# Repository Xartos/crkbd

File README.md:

# Fork purpose

The purpose of this fork is to replace the audio jack `ST-0277D00-052-142` for the v4 model and replace it with the `PJ-606-6A`

# Corne keyboard

The Corne keyboard is a split keyboard with 3x6 column staggered keys
and 3 thumb keys, based on [Helix](https://github.com/MakotoKurauchi/helix).
Crkbd stands for Corne Keyboard.

## Latest versions
- corne-cherry: for Cherry MX compatible switches

  - v4 Hotswappable ([JP](docs/corne-cherry/v4/buildguide_jp.md)/[EN](docs/corne-cherry/v4/buildguide_en.md))
  - v4 Soldering (will be released)
- corne-chocolate: for Kailh choc v1 and v2 switches
  - v4 Hotswappable ([JP](docs/corne-chocolate/v4/buildguide_jp.md)/[EN](docs/corne-chocolate/v4/buildguide_en.md)):
  - v4 Soldering (will be released)

## Old versions

- corne-classic: for Cherry MX compatible switches 
  - v1 Soldering: ([JP](docs/corne-classic/buildguide_jp.md)/[EN](docs/corne-classic/buildguide_en.md))
- corne-cherry: for Cherry MX compatible switches
  - v2 Hotswappable: ([JP](docs/corne-cherry/v2/buildguide_jp.md)/[EN](docs/corne-cherry/v2/buildguide_en.md))
  - v2 Hotswappable tilting version: ([tilting, JP](docs/corne-cherry/v2/buildguide_tilting_tenting_plate_jp.md)/[tilting, EN](docs/corne-cherry/v2/buildguide_tilting_tenting_plate_en.md)):
  - v3 Hotswappable: ([JP](docs/corne-cherry/v3/buildguide_jp.md)/[EN](docs/corne-cherry/v3/buildguide_en.md))
- corne-chocolate: for Kailh choc v1 switches
  - v2 Hotswappable: ([JP](docs/corne-chocolate/v2/buildguide_jp.md)/[EN](docs/corne-chocolate/v2/buildguide_en.md)):
- corne-light: for easy build with a simple PCB
  - v1 Soldering: ([JP](docs/corne-light/v1/buildguide_jp.md)/[EN](docs/corne-light/v1/buildguide_en.md)):
  - v2 Soldering: ([JP](docs/corne-light/v2/buildguide_low_edition_jp.md)/[EN](docs/corne-light/v2/buildguide_low_edition_en.md)):

## Images

### Cherry

### Chocolate

### Drawing

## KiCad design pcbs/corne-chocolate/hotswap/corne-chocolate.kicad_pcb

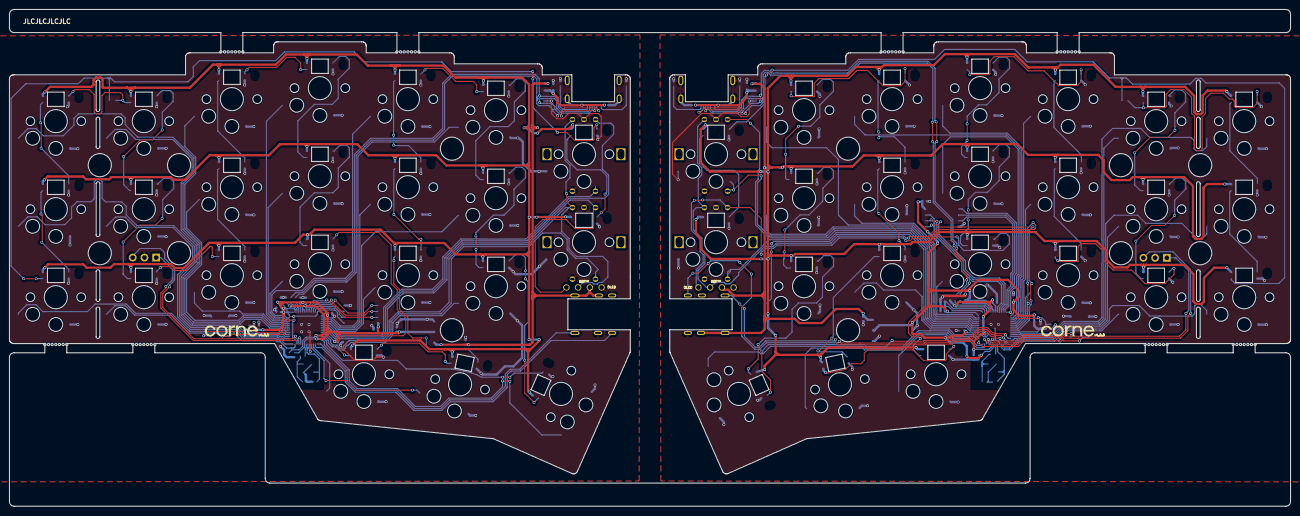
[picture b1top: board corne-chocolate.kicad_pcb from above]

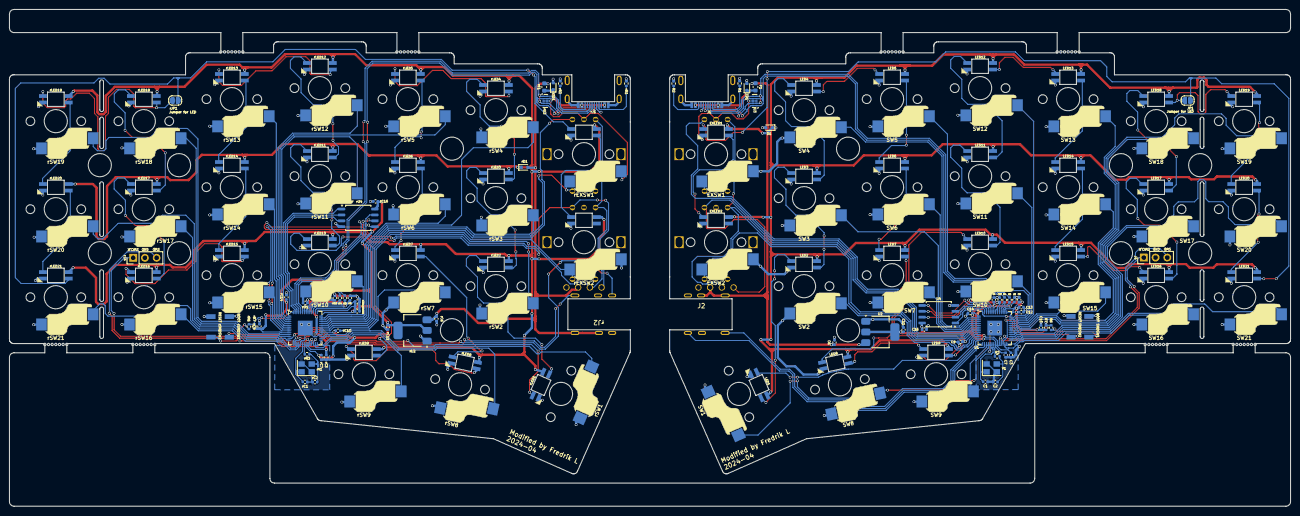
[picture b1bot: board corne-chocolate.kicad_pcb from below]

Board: 2 copper layers, 277.2 x 107.5 mm, 176 parts (166 on the bottom side), 152 nets.

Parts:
BT1, BT2, BT3, BT4: Breakaway Tabs; Breakaway_Tabs
C1, C2: 27p; C_0402_1005Metric
C3, C4, C7, C9, C10, C12, C13, C14, C15: 100n; C_0402_1005Metric
C5, C8, C16: 1u; C_0402_1005Metric
C6, C11: 10u; C_0402_1005Metric
D1: 1N4148WT; D_SOD-523
EXLED1, EXLED2: YS-SK6812MINI-E
EXSW1, EXSW2: RotaryEncoder_Switch; keyswitch_choc12_hotswap_1u_rotary_encoder_ec12
F1: BSMD0603-050-12V; Fuse_0603_1608Metric
J1: TYPE-C-31-M-13C
J2: PJ-606-6A
J3: Conn_01x04; OLED
J4: Conn_01x03; PinHeader_1x03_P2.54mm_Vertical
JP1: SolderJumper_2_Bridged; SolderJumper-2_P1.3mm_Open_RoundedPad1.0x1.5mm
LED1, LED2, LED3, LED4, LED5, LED6, LED7, LED8, LED9, LED10, LED11, LED12, LED13, LED14, LED15, LED16, LED17, LED18, LED19, LED20, LED21: YS-SK6812MINI-E
R1, R2: 5.1k; R_0402_1005Metric
R3, R6: 1k; R_0402_1005Metric
R4, R5: 27; R_0402_1005Metric
R7: 10k; R_0402_1005Metric
SMDSW1, SMDSW2: TS-1088R-02026
SW1: SW_Push; keyswitch_choc12_hotswap_1.5u
SW2, SW3, SW4, SW5, SW6, SW7, SW8, SW9, SW10, SW11, SW12, SW13, SW14, SW15, SW16, SW17, SW18, SW19, SW20, SW21: SW_Push; keyswitch_choc12_hotswap_1u
U1: RP2040; QFN-56-1EP_7x7mm_P0.4mm_EP3.2x3.2mm
U2: NCP1117LPST33T3G; SOT-223-3_TabPin2
U3: TPD4E05U06DQAR; USON-10_2.5x1.0mm_P0.5mm
U4: W25Q128JVSIQ; SOIC-8_5.23x5.23mm_P1.27mm
Y1: 12MHz 18pF; Crystal_SMD_3225-4Pin_3.2x2.5mm
ZD1: ESD5Z5V0C; D_SOD-523
rBT1, rBT2, rBT3, rBT4: Breakaway Tabs; Breakaway_Tabs
rC1, rC2: 27p; C_0402_1005Metric
rC3, rC4, rC7, rC9, rC10, rC12, rC13, rC14, rC15: 100n; C_0402_1005Metric
rC5, rC8, rC16: 1u; C_0402_1005Metric
rC6, rC11: 10u; C_0402_1005Metric
rD1: 1N4148WT; D_SOD-523
rEXLED1, rEXLED2: YS-SK6812MINI-E
rEXSW1, rEXSW2: RotaryEncoder_Switch; keyswitch_choc12_hotswap_1u_rotary_encoder_ec12
rF1: BSMD0603-050-12V; Fuse_0603_1608Metric
rJ1: TYPE-C-31-M-13C
rJ2: PJ-606-6A
rJ3: Conn_01x04; OLED
rJ4: Conn_01x03; PinHeader_1x03_P2.54mm_Vertical
rJP1: SolderJumper_2_Bridged; SolderJumper-2_P1.3mm_Open_RoundedPad1.0x1.5mm
rLED1, rLED2, rLED3, rLED4, rLED5, rLED6, rLED7, rLED8, rLED9, rLED10, rLED11, rLED12, rLED13, rLED14, rLED15, rLED16, rLED17, rLED18, rLED19, rLED20, rLED21: YS-SK6812MINI-E
rR1, rR2: 5.1k; R_0402_1005Metric
rR3, rR6: 1k; R_0402_1005Metric
rR4, rR5: 27; R_0402_1005Metric
rR7: 10k; R_0402_1005Metric
rSMDSW1, rSMDSW2: TS-1088R-02026
rSW1: SW_Push; keyswitch_choc12_hotswap_1.5u
rSW2, rSW3, rSW4, rSW5, rSW6, rSW7, rSW8, rSW9, rSW10, rSW11, rSW12, rSW13, rSW14, rSW15, rSW16, rSW17, rSW18, rSW19, rSW20, rSW21: SW_Push; keyswitch_choc12_hotswap_1u
rU1: RP2040; QFN-56-1EP_7x7mm_P0.4mm_EP3.2x3.2mm
rU2: NCP1117LPST33T3G; SOT-223-3_TabPin2
rU3: TPD4E05U06DQAR; USON-10_2.5x1.0mm_P0.5mm
rU4: W25Q128JVSIQ; SOIC-8_5.23x5.23mm_P1.27mm
rY1: 12MHz 18pF; Crystal_SMD_3225-4Pin_3.2x2.5mm
rZD1: ESD5Z5V0C; D_SOD-523

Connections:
+1V1: C3.1, C4.1, C5.1, U1.23 (DVDD), U1.45 (VREG_VOUT), U1.50 (DVDD)
+1V1R: rC3.1, rC4.1, rC5.1, rU1.23 (DVDD), rU1.45 (VREG_VOUT), rU1.50 (DVDD)
+3V3: C7.1, C8.1, C9.1, C10.1, C11.1, C12.1, C13.1, C14.1, C15.1, C16.1, R7.2, U1.1 (IOVDD), U1.10 (IOVDD), U1.22 (IOVDD), U1.32 (GPIO21), U1.33 (IOVDD), U1.42 (IOVDD), U1.43 (ADC_AVDD), U1.44 (VREG_IN), U1.48 (USB_VDD), U1.49 (IOVDD), U2.2 (VO), U4.8 (VCC)
+3V3R: rC7.1, rC8.1, rC9.1, rC10.1, rC11.1, rC12.1, rC13.1, rC14.1, rC15.1, rC16.1, rR7.2, rU1.1 (IOVDD), rU1.10 (IOVDD), rU1.22 (IOVDD), rU1.33 (IOVDD), rU1.42 (IOVDD), rU1.43 (ADC_AVDD), rU1.44 (VREG_IN), rU1.48 (USB_VDD), rU1.49 (IOVDD), rU2.2 (VO), rU4.8 (VCC)
+5V: C6.1, D1.2 (A), F1.2, J2.T, J3.3, U2.3 (VI)
+5VR: rC6.1, rD1.2 (A), rF1.2, rJ2.T, rJ3.3, rU2.3 (VI)
/left/D+: J1.A6 (D+), J1.B6 (D+), R4.1, U3.1 (D1+), U3.4 (D2+), U3.7 (NC), U3.10 (NC)
/left/D-: J1.A7 (D-), J1.B7 (D-), R5.2, U3.2 (D1-), U3.5 (D2-), U3.6 (NC), U3.9 (NC)
/left/KEY1: SW1.1, U1.14 (GPIO11)
/left/KEY2: SW2.1, U1.12 (GPIO9)
/left/KEY3: SW3.1, U1.4 (GPIO2)
/left/KEY4: SW4.1, U1.2 (GPIO0)
/left/KEY5: SW5.1, U1.41 (GPIO29_ADC3)
/left/KEY6: SW6.1, U1.3 (GPIO1)
/left/KEY7: SW7.1, U1.5 (GPIO3)
/left/KEY8: SW8.1, U1.18 (GPIO15)
/left/KEY9: SW9.1, U1.17 (GPIO14)
/left/KEY10: SW10.1, U1.40 (GPIO28_ADC2)
/left/KEY11: SW11.1, U1.39 (GPIO27_ADC1)
/left/KEY12: SW12.1, U1.38 (GPIO26_ADC0)
/left/KEY13: SW13.1, U1.35 (GPIO23)
/left/KEY14: SW14.1, U1.36 (GPIO24)
/left/KEY15: SW15.1, U1.37 (GPIO25)
/left/KEY16: SW16.1, U1.27 (GPIO16)
/left/KEY17: SW17.1, U1.29 (GPIO18)
/left/KEY18: SW18.1, U1.31 (GPIO20)
/left/KEY19: SW19.1, U1.34 (GPIO22)
/left/KEY20: SW20.1, U1.30 (GPIO19)
/left/KEY21: SW21.1, U1.28 (GPIO17)
/left/KEYEX1: EXSW1.S2, U1.6 (GPIO4)
/left/KEYEX2: EXSW2.S2, U1.11 (GPIO8)
/left/LED: LED1.4 (DIN), U1.13 (GPIO10)
/left/QSPI_SCLK: U1.52 (QSPI_SCLK), U4.6 (CLK)
/left/QSPI_SD0: U1.53 (QSPI_SD0), U4.5 (DI(IO0))
/left/QSPI_SD1: U1.55 (QSPI_SD1), U4.2 (DO(IO1))
/left/QSPI_SD2: U1.54 (QSPI_SD2), U4.3 (IO2)
/left/QSPI_SD3: U1.51 (QSPI_SD3), U4.7 (IO3)
/left/QSPI_SS: R6.1, R7.1, U1.56 (QSPI_SS), U4.1 (~CS)
/left/RE0A: EXSW1.A, U1.7 (GPIO5)
/left/RE1A: EXSW2.A, J3.1, U1.8 (GPIO6)
/left/REB: EXSW1.B, EXSW2.B, J3.2, U1.9 (GPIO7)
/left/RX: J2.R1, U1.16 (GPIO13)
/left/SWCLK: J4.1, U1.24 (SWCLK)
/left/SWD: J4.3, U1.25 (SWD)
/left/TX: J2.R2, U1.15 (GPIO12)
/right/D+: rJ1.A6 (D+), rJ1.B6 (D+), rR4.1, rU3.1 (D1+), rU3.4 (D2+), rU3.7 (NC), rU3.10 (NC)
/right/D-: rJ1.A7 (D-), rJ1.B7 (D-), rR5.2, rU3.2 (D1-), rU3.5 (D2-), rU3.6 (NC), rU3.9 (NC)
/right/KEY1: rSW1.1, rU1.30 (GPIO19)
/right/KEY2: rSW2.1, rU1.34 (GPIO22)
/right/KEY3: rSW3.1, rU1.38 (GPIO26_ADC0)
/right/KEY4: rSW4.1, rU1.39 (GPIO27_ADC1)
/right/KEY5: rSW5.1, rU1.3 (GPIO1)
/right/KEY6: rSW6.1, rU1.40 (GPIO28_ADC2)
/right/KEY7: rSW7.1, rU1.31 (GPIO20)
/right/KEY8: rSW8.1, rU1.28 (GPIO17)
/right/KEY9: rSW9.1, rU1.27 (GPIO16)
/right/KEY10: rSW10.1, rU1.41 (GPIO29_ADC3)
/right/KEY11: rSW11.1, rU1.2 (GPIO0)
/right/KEY12: rSW12.1, rU1.4 (GPIO2)
/right/KEY13: rSW13.1, rU1.5 (GPIO3)
/right/KEY14: rSW14.1, rU1.6 (GPIO4)
/right/KEY15: rSW15.1, rU1.7 (GPIO5)
/right/KEY16: rSW16.1, rU1.29 (GPIO18)
/right/KEY17: rSW17.1, rU1.17 (GPIO14)
/right/KEY18: rSW18.1, rU1.12 (GPIO9)
/right/KEY19: rSW19.1, rU1.11 (GPIO8)
/right/KEY20: rSW20.1, rU1.14 (GPIO11)
/right/KEY21: rSW21.1, rU1.18 (GPIO15)
/right/KEYEX1: rEXSW1.S2, rU1.37 (GPIO25)
/right/KEYEX2: rEXSW2.S2, rU1.35 (GPIO23)
/right/LED: rLED1.4 (DIN), rU1.13 (GPIO10)
/right/QSPI_SCLK: rU1.52 (QSPI_SCLK), rU4.6 (CLK)
/right/QSPI_SD0: rU1.53 (QSPI_SD0), rU4.5 (DI(IO0))
/right/QSPI_SD1: rU1.55 (QSPI_SD1), rU4.2 (DO(IO1))
/right/QSPI_SD2: rU1.54 (QSPI_SD2), rU4.3 (IO2)
/right/QSPI_SD3: rU1.51 (QSPI_SD3), rU4.7 (IO3)
/right/QSPI_SS: rR6.1, rR7.1, rU1.56 (QSPI_SS), rU4.1 (~CS)
/right/RE0A: rEXSW1.A, rU1.36 (GPIO24)
/right/RE1A: rEXSW2.A, rJ3.1, rU1.8 (GPIO6)
/right/REB: rEXSW1.B, rEXSW2.B, rJ3.2, rU1.9 (GPIO7)
/right/RX: rJ2.R2, rU1.16 (GPIO13)
/right/SWCLK: rJ4.1, rU1.24 (SWCLK)
/right/SWD: rJ4.3, rU1.25 (SWD)
/right/TX: rJ2.R1, rU1.15 (GPIO12)
GND: C1.2, C2.2, C3.2, C4.2, C5.2, C6.2, C7.2, C8.2, C9.2, C10.2, C11.2, C12.2, C13.2, C14.2, C15.2, C16.2, EXLED1.3 (VSS), EXLED2.3 (VSS), EXSW1.C, EXSW1.S1, EXSW2.C, EXSW2.S1, J1.A1 (GND), J1.A12 (GND), J1.B1 (GND), J1.B12 (GND), J1.S1 (SHIELD), J2.S, J3.4, J4.2, LED1.3 (VSS), LED2.3 (VSS), LED3.3 (VSS), LED4.3 (VSS), LED5.3 (VSS), LED6.3 (VSS), LED7.3 (VSS), LED8.3 (VSS), LED9.3 (VSS), LED10.3 (VSS), LED11.3 (VSS), LED12.3 (VSS), LED13.3 (VSS), LED14.3 (VSS), LED15.3 (VSS), LED16.3 (VSS), LED17.3 (VSS), LED18.3 (VSS), LED19.3 (VSS), LED20.3 (VSS), LED21.3 (VSS), R1.1, R2.1, SMDSW1.1, SMDSW2.1, SW1.2, SW2.2, SW3.2, SW4.2, SW5.2, SW6.2, SW7.2, SW8.2, SW9.2, SW10.2, SW11.2, SW12.2, SW13.2, SW14.2, SW15.2, SW16.2, SW17.2, SW18.2, SW19.2, SW20.2, SW21.2, U1.19 (TESTEN), U1.57 (GND), U2.1 (GND), U3.3 (GND), U3.8 (GND), U4.4 (GND), Y1.2, Y1.4, ZD1.2 (A)
GNDR: rC1.2, rC2.2, rC3.2, rC4.2, rC5.2, rC6.2, rC7.2, rC8.2, rC9.2, rC10.2, rC11.2, rC12.2, rC13.2, rC14.2, rC15.2, rC16.2, rEXLED1.3 (VSS), rEXLED2.3 (VSS), rEXSW1.C, rEXSW1.S1, rEXSW2.C, rEXSW2.S1, rJ1.A1 (GND), rJ1.A12 (GND), rJ1.B1 (GND), rJ1.B12 (GND), rJ1.S1 (SHIELD), rJ2.S, rJ3.4, rJ4.2, rLED1.3 (VSS), rLED2.3 (VSS), rLED3.3 (VSS), rLED4.3 (VSS), rLED5.3 (VSS), rLED6.3 (VSS), rLED7.3 (VSS), rLED8.3 (VSS), rLED9.3 (VSS), rLED10.3 (VSS), rLED11.3 (VSS), rLED12.3 (VSS), rLED13.3 (VSS), rLED14.3 (VSS), rLED15.3 (VSS), rLED16.3 (VSS), rLED17.3 (VSS), rLED18.3 (VSS), rLED19.3 (VSS), rLED20.3 (VSS), rLED21.3 (VSS), rR1.1, rR2.1, rSMDSW1.1, rSMDSW2.1, rSW1.2, rSW2.2, rSW3.2, rSW4.2, rSW5.2, rSW6.2, rSW7.2, rSW8.2, rSW9.2, rSW10.2, rSW11.2, rSW12.2, rSW13.2, rSW14.2, rSW15.2, rSW16.2, rSW17.2, rSW18.2, rSW19.2, rSW20.2, rSW21.2, rU1.19 (TESTEN), rU1.32 (GPIO21), rU1.57 (GND), rU2.1 (GND), rU3.3 (GND), rU3.8 (GND), rU4.4 (GND), rY1.2, rY1.4, rZD1.2 (A)
unnamed: C2.1, R3.1, Y1.3
unnamed: D1.1 (K), EXLED1.1 (VDD), EXLED2.1 (VDD), LED1.1 (VDD), LED2.1 (VDD), LED3.1 (VDD), LED4.1 (VDD), LED5.1 (VDD), LED6.1 (VDD), LED7.1 (VDD), LED8.1 (VDD), LED9.1 (VDD), LED10.1 (VDD), LED11.1 (VDD), LED12.1 (VDD), LED13.1 (VDD), LED14.1 (VDD), LED15.1 (VDD), LED16.1 (VDD), LED17.1 (VDD), LED18.1 (VDD), LED19.1 (VDD), LED20.1 (VDD), LED21.1 (VDD)
unnamed: EXLED1.4 (DIN), JP1.2 (B), LED21.2 (DOUT)
unnamed: EXLED1.2 (DOUT), EXLED2.4 (DIN)
unnamed: J1.A5 (CC1), R1.2
unnamed: J1.B5 (CC2), R2.2
unnamed: JP1.1 (A), LED18.2 (DOUT), LED19.4 (DIN)
unnamed: LED1.2 (DOUT), LED2.4 (DIN)
unnamed: LED2.2 (DOUT), LED3.4 (DIN)
unnamed: LED3.2 (DOUT), LED4.4 (DIN)
unnamed: LED4.2 (DOUT), LED5.4 (DIN)
unnamed: LED5.2 (DOUT), LED6.4 (DIN)
unnamed: LED6.2 (DOUT), LED7.4 (DIN)
unnamed: LED7.2 (DOUT), LED8.4 (DIN)
unnamed: LED8.2 (DOUT), LED9.4 (DIN)
unnamed: LED9.2 (DOUT), LED10.4 (DIN)
unnamed: LED10.2 (DOUT), LED11.4 (DIN)
unnamed: LED11.2 (DOUT), LED12.4 (DIN)
unnamed: LED12.2 (DOUT), LED13.4 (DIN)
unnamed: LED13.2 (DOUT), LED14.4 (DIN)
unnamed: LED14.2 (DOUT), LED15.4 (DIN)
unnamed: LED15.2 (DOUT), LED16.4 (DIN)
unnamed: LED16.2 (DOUT), LED17.4 (DIN)
unnamed: LED17.2 (DOUT), LED18.4 (DIN)
unnamed: LED19.2 (DOUT), LED20.4 (DIN)
unnamed: LED20.2 (DOUT), LED21.4 (DIN)
unnamed: R6.2, SMDSW1.2
unnamed: SMDSW2.2, U1.26 (RUN)
unnamed: R5.1, U1.46 (USB_DM)
unnamed: R4.2, U1.47 (USB_DP)
unnamed: C1.1, U1.20 (XIN), Y1.1
unnamed: R3.2, U1.21 (XOUT)
unnamed: rC2.1, rR3.1, rY1.3
unnamed: rD1.1 (K), rEXLED1.1 (VDD), rEXLED2.1 (VDD), rLED1.1 (VDD), rLED2.1 (VDD), rLED3.1 (VDD), rLED4.1 (VDD), rLED5.1 (VDD), rLED6.1 (VDD), rLED7.1 (VDD), rLED8.1 (VDD), rLED9.1 (VDD), rLED10.1 (VDD), rLED11.1 (VDD), rLED12.1 (VDD), rLED13.1 (VDD), rLED14.1 (VDD), rLED15.1 (VDD), rLED16.1 (VDD), rLED17.1 (VDD), rLED18.1 (VDD), rLED19.1 (VDD), rLED20.1 (VDD), rLED21.1 (VDD)
unnamed: rEXLED1.4 (DIN), rJP1.2 (B), rLED21.2 (DOUT)
unnamed: rEXLED1.2 (DOUT), rEXLED2.4 (DIN)
unnamed: rJ1.A5 (CC1), rR1.2
unnamed: rJ1.B5 (CC2), rR2.2
unnamed: rJP1.1 (A), rLED18.2 (DOUT), rLED19.4 (DIN)
unnamed: rLED1.2 (DOUT), rLED2.4 (DIN)
unnamed: rLED2.2 (DOUT), rLED3.4 (DIN)
unnamed: rLED3.2 (DOUT), rLED4.4 (DIN)
unnamed: rLED4.2 (DOUT), rLED5.4 (DIN)
unnamed: rLED5.2 (DOUT), rLED6.4 (DIN)
unnamed: rLED6.2 (DOUT), rLED7.4 (DIN)
unnamed: rLED7.2 (DOUT), rLED8.4 (DIN)
unnamed: rLED8.2 (DOUT), rLED9.4 (DIN)
unnamed: rLED9.2 (DOUT), rLED10.4 (DIN)
unnamed: rLED10.2 (DOUT), rLED11.4 (DIN)
unnamed: rLED11.2 (DOUT), rLED12.4 (DIN)
unnamed: rLED12.2 (DOUT), rLED13.4 (DIN)
unnamed: rLED13.2 (DOUT), rLED14.4 (DIN)
unnamed: rLED14.2 (DOUT), rLED15.4 (DIN)
unnamed: rLED15.2 (DOUT), rLED16.4 (DIN)
unnamed: rLED16.2 (DOUT), rLED17.4 (DIN)
unnamed: rLED17.2 (DOUT), rLED18.4 (DIN)
unnamed: rLED19.2 (DOUT), rLED20.4 (DIN)
unnamed: rLED20.2 (DOUT), rLED21.4 (DIN)
unnamed: rR6.2, rSMDSW1.2
unnamed: rSMDSW2.2, rU1.26 (RUN)
unnamed: rR5.1, rU1.46 (USB_DM)
unnamed: rR4.2, rU1.47 (USB_DP)
unnamed: rC1.1, rU1.20 (XIN), rY1.1
unnamed: rR3.2, rU1.21 (XOUT)
VBUS: F1.1, J1.A4 (VBUS), J1.A9 (VBUS), J1.B4 (VBUS), J1.B9 (VBUS), ZD1.1 (K)
VBUSR: rF1.1, rJ1.A4 (VBUS), rJ1.A9 (VBUS), rJ1.B4 (VBUS), rJ1.B9 (VBUS), rZD1.1 (K)

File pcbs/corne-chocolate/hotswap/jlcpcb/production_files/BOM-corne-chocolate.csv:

Designator,Footprint,Quantity,Value,LCSC Part #
"C1, C2, rC1, rC2",0402,4,27p,
"C10, C12, C13, C14, C15, C3, C4, C7, C9, rC10, rC12, rC13, rC14, rC15, rC3, rC4, rC7, rC9",0402,18,100n,
"C11, C6, rC11, rC6",0402,4,10u,
"C16, C5, C8, rC16, rC5, rC8",0402,6,1u,
"D1, rD1",D_SOD-523,2,1N4148WT,C232841
"EXLED1, EXLED2, LED1, LED10, LED11, LED12, LED13, LED14, LED15, LED16, LED17, LED18, LED19, LED2, LED20, LED21, LED3, LED4, LED5, LED6, LED7, LED8, LED9, rEXLED1, rEXLED2, rLED1, rLED10, rLED11, rLED12, rLED13, rLED14, rLED15, rLED16, rLED17, rLED18, rLED19, rLED2, rLED20, rLED21, rLED3, rLED4, rLED5, rLED6, rLED7, rLED8, rLED9",YS-SK6812MINI-E,46,YS-SK6812MINI-E,C5149201
"EXSW1, EXSW2, rEXSW1, rEXSW2",keyswitch_choc12_hotswap_1u_rotary_encoder_ec12,4,RotaryEncoder_Switch,C5333465
"F1, rF1",0603,2,BSMD0603-050-12V,C2844464
"J1, rJ1",TYPE-C-31-M-13C,2,TYPE-C-31-M-13C,C2848620
"J2, rJ2",PJ-606-6A,2,PJ-606-6A,C145806
"R1, R2, rR1, rR2",0402,4,5.1k,
"R3, R6, rR3, rR6",0402,4,1k,
"R4, R5, rR4, rR5",0402,4,27,
"R7, rR7",0402,2,10k,
"SMDSW1, SMDSW2, rSMDSW1, rSMDSW2",TS-1088R-02026,4,TS-1088R-02026,C455280
"SW1, rSW1",keyswitch_choc12_hotswap_1.5u,2,SW_Push,C5333465
"SW10, SW11, SW12, SW13, SW14, SW15, SW16, SW17, SW18, SW19, SW2, SW20, SW21, SW3, SW4, SW5, SW6, SW7, SW8, SW9, rSW10, rSW11, rSW12, rSW13, rSW14, rSW15, rSW16, rSW17, rSW18, rSW19, rSW2, rSW20, rSW21, rSW3, rSW4, rSW5, rSW6, rSW7, rSW8, rSW9",keyswitch_choc12_hotswap_1u,40,SW_Push,C5333465
"U1, rU1",QFN-56-1EP_7x7mm_P0.4mm_EP3.2x3.2mm,2,RP2040,C2040
"U2, rU2",SOT-223-3_TabPin2,2,NCP1117LPST33T3G,C146799
"U3, rU3",USON-10_2.5x1.0mm_P0.5mm,2,TPD4E05U06DQAR,C138714
"U4, rU4",SOIC-8_5.23x5.23mm_P1.27mm,2,W25Q128JVSIQ,C113767
"Y1, rY1",Crystal_SMD_3225-4Pin_3.2x2.5mm,2,12MHz 18pF,C91749
"ZD1, rZD1",D_SOD-523,2,ESD5Z5V0C,C2901325

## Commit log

2024-04-23 Kicad automatically updated footprints
2024-04-23 Added PJ-606-6A footprint
2024-04-23 Updated pcb for corne-chocolate to use PJ-606-6A audio jack
2024-04-23 Updated JLCPCB production files for corne-chocolate
2024-04-23 Updated README with fork purpose
2024-04-29 Moved VIAs in compliance with JLCPCB engineers
